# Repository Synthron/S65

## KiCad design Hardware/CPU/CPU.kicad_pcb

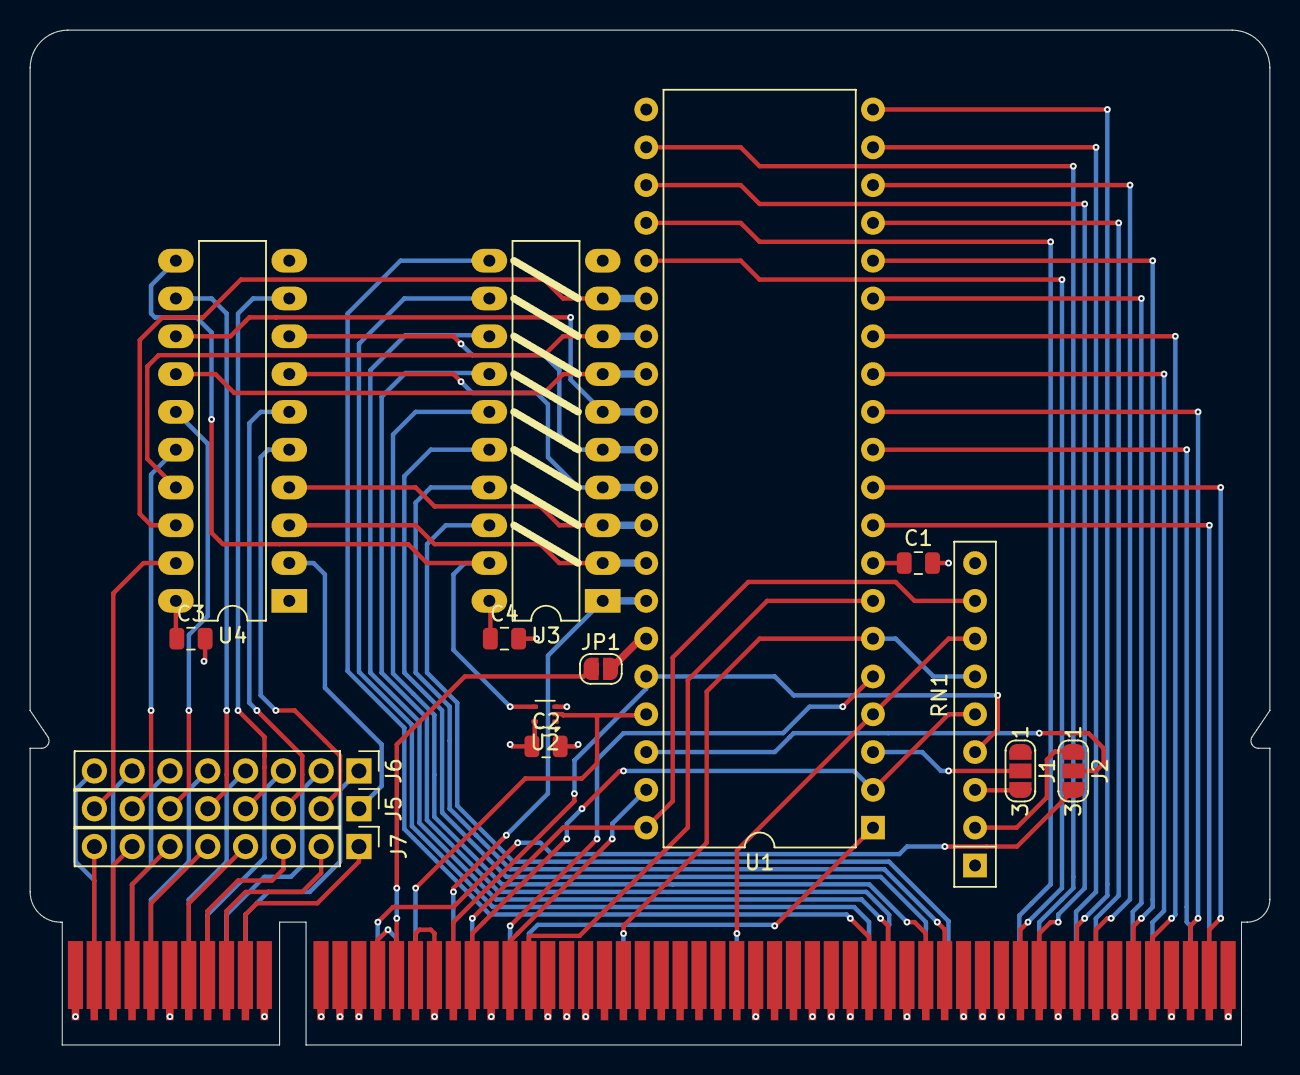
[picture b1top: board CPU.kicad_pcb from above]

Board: 4 copper layers, 83.3 x 68.2 mm, 16 parts (1 on the bottom side), 78 nets.

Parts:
C1, C2, C3, C4: 100n; C_0805_2012Metric
J1: ABORT; SolderJumper-3_P1.3mm_Open_RoundedPad1.0x1.5mm_NumberLabels
J2: SO/MX; SolderJumper-3_P1.3mm_Open_RoundedPad1.0x1.5mm_NumberLabels
J3: Bus_PCI_6502; BUS_PCI
J5: Bank Bridge A; PinHeader_1x08_P2.54mm_Vertical
J6: Bank Bridge B; PinHeader_1x08_P2.54mm_Vertical
J7: Bank Bridge C; PinHeader_1x08_P2.54mm_Vertical
JP1: E; SolderJumper-2_P1.3mm_Open_RoundedPad1.0x1.5mm
RN1: 3k3; R_Array_SIP9
U1: 65C02 / 65816; DIP-40_W15.24mm
U2: 74LVC1GU04DRL; SOT-553
U3: 74HC245; DIP-20_W7.62mm_LongPads
U4: 74HC373; DIP-20_W7.62mm_LongPads

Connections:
+5V: C1.1, C2.1, C3.1, C4.1, J3.A14 (5V), J3.A22 (5V), J3.A36 (5V), J3.A47 (5V), J3.B14 (5V), J3.B22 (5V), J3.B36 (5V), J3.B47 (5V), RN1.1 (common), U1.8 (VDD), U2.5 (VCC), U3.20 (VCC), U4.20 (VCC)
+9V: J3.A49 (9V), J3.B49 (9V)
/A0: J3.B2 (A0), U1.9 (A0)
/A1: J3.A2 (A1), U1.10 (A1)
/A2: J3.B3 (A2), U1.11 (A2)
/A3: J3.A3, U1.12 (A3)
/A4: J3.B5 (A4), U1.13 (A4)
/A5: J3.A5, U1.14 (A5)
/A6: J3.B6 (A6), U1.15 (A6)
/A7: J3.A6 (A7), U1.16 (A7)
/A8: J3.B8 (A8), U1.17 (A8)
/A9: J3.A8 (A9), U1.18 (A9)
/A10: J3.B9 (A10), U1.19 (A10)
/A11: J3.A9 (A11), U1.20 (A11)
/A12: J3.B11 (A12), U1.22 (A12)
/A13: J3.A11 (A13), U1.23 (A13)
/A14: J3.B12 (A14), U1.24 (A14)
/A15: J3.A12 (A15), U1.25 (A15)
/BA0: J5.1, U4.2 (O0)
/BA1: J5.2, U4.5 (O1)
/BA2: J5.3, U4.6 (O2)
/BA3: J5.4, U4.9 (O3)
/BA4: J5.5, U4.12 (O4)
/BA5: J5.6, U4.15 (O5)
/BA6: J5.7, U4.16 (O6)
/BA7: J5.8, U4.19 (O7)
/CLK: J3.B44 (CLK), U1.37 (ϕ0), U2.2
/D0: J3.B16 (D0), U3.18 (B0)
/D1: J3.A16 (D1), U3.17 (B1)
/D2: J3.B17 (D2), U3.16 (B2)
/D3: J3.A17 (D3), U3.15 (B3)
/D4: J3.B19 (D4), U3.14 (B4)
/D5: J3.A19 (D5), U3.13 (B5)
/D6: J3.B20 (D6), U3.12 (B6)
/D7: J3.A20 (D7), U3.11 (B7)
/E: J3.A45 (E), JP1.1 (A)
/M/X: J2.3, J3.B46 (M/~X)
/RAM_0: J3.A53 (RAM0), J7.1
/RAM_1: J3.A54 (RAM1), J7.2
/RAM_2: J3.A55 (RAM2), J7.3
/RAM_3: J3.A56 (RAM3), J7.4
/RAM_4: J3.A58 (RAM4), J7.5
/RAM_5: J3.A59 (RAM5), J7.6
/RAM_6: J3.A60 (RAM6), J7.7
/RAM_7: J3.A61 (RAM7), J7.8
/ROM_0: J3.B53 (ROM0), J6.1
/ROM_1: J3.B54 (ROM1), J6.2
/ROM_2: J3.B55 (ROM2), J6.3
/ROM_3: J3.B56 (ROM3), J6.4
/ROM_4: J3.B58 (ROM4), J6.5
/ROM_5: J3.B59 (ROM5), J6.6
/ROM_6: J3.B60 (ROM6), J6.7
/ROM_7: J3.B61 (ROM7), J6.8
/R/~W: J3.B42 (R/~W), U1.34 (R/~W), U3.1 (A->B)
/SYNC_VPA: J3.A38 (Sync/VPA), U1.7 (SYNC)
/~BE: J3.A42 (~BE), RN1.4 (R3), U1.36 (BE)
/~IRQ: J3.B27 (~IRQ), RN1.7 (R6), U1.4 (~IRQ)
/~ML: J3.B39 (~ML), U1.5 (~ML)
/~NMI: J3.B33 (~NMI), RN1.6 (R5), U1.6 (~NMI)
/~RDY: J3.A41 (~RDY), RN1.5 (R4), U1.2 (RDY)
/~RES: J3.B41 (~RES), RN1.8 (R7), U1.40 (~RES)
/~VP: J3.B38 (~VP), U1.1 (~VP)
/Ø2/VDA: J3.A39 (Ø2/VDA), U1.39 (ϕ2)
GND: C1.2, C2.2, C3.2, C4.2, J3.A1 (GND), J3.A4 (GND), J3.A7 (GND), J3.A10 (GND), J3.A13 (GND), J3.A15 (GND), J3.A18 (GND), J3.A21 (GND), J3.A23 (GND), J3.A26 (GND), J3.A35 (GND), J3.A37 (GND), J3.A40 (GND), J3.A43 (GND), J3.A44 (GND), J3.A46 (GND), J3.A48 (GND), J3.A52 (GND), J3.A57 (GND), J3.A62 (GND), J3.B1 (GND), J3.B4 (GND), J3.B7 (GND), J3.B10 (GND), J3.B13 (GND), J3.B15 (GND), J3.B18 (GND), J3.B21 (GND), J3.B23 (GND), J3.B26 (GND), J3.B35 (GND), J3.B37 (GND), J3.B40 (GND), J3.B43 (GND), J3.B45 (GND), J3.B48 (GND), J3.B52 (GND), J3.B57 (GND), J3.B62 (GND), U1.21 (VSS), U2.3 (GND), U3.10 (GND), U4.10 (GND)
unnamed: J1.2, U1.3 (ϕ1)
unnamed: J1.3, RN1.3 (R2)
unnamed: J2.1, RN1.2 (R1)
unnamed: J2.2, U1.38 (~SO)
unnamed: JP1.2 (B), U1.35 (nc)
unnamed: U1.33 (D0), U3.2 (A0), U4.3 (D0)
unnamed: U1.32 (D1), U3.3 (A1), U4.4 (D1)
unnamed: U1.31 (D2), U3.4 (A2), U4.7 (D2)
unnamed: U1.30 (D3), U3.5 (A3), U4.8 (D3)
unnamed: U1.29 (D4), U3.6 (A4), U4.13 (D4)
unnamed: U1.28 (D5), U3.7 (A5), U4.14 (D5)
unnamed: U1.27 (D6), U3.8 (A6), U4.17 (D6)
unnamed: U1.26 (D7), U3.9 (A7), U4.18 (D7)
unnamed: U2.4, U3.19 (CE), U4.11 (LE)

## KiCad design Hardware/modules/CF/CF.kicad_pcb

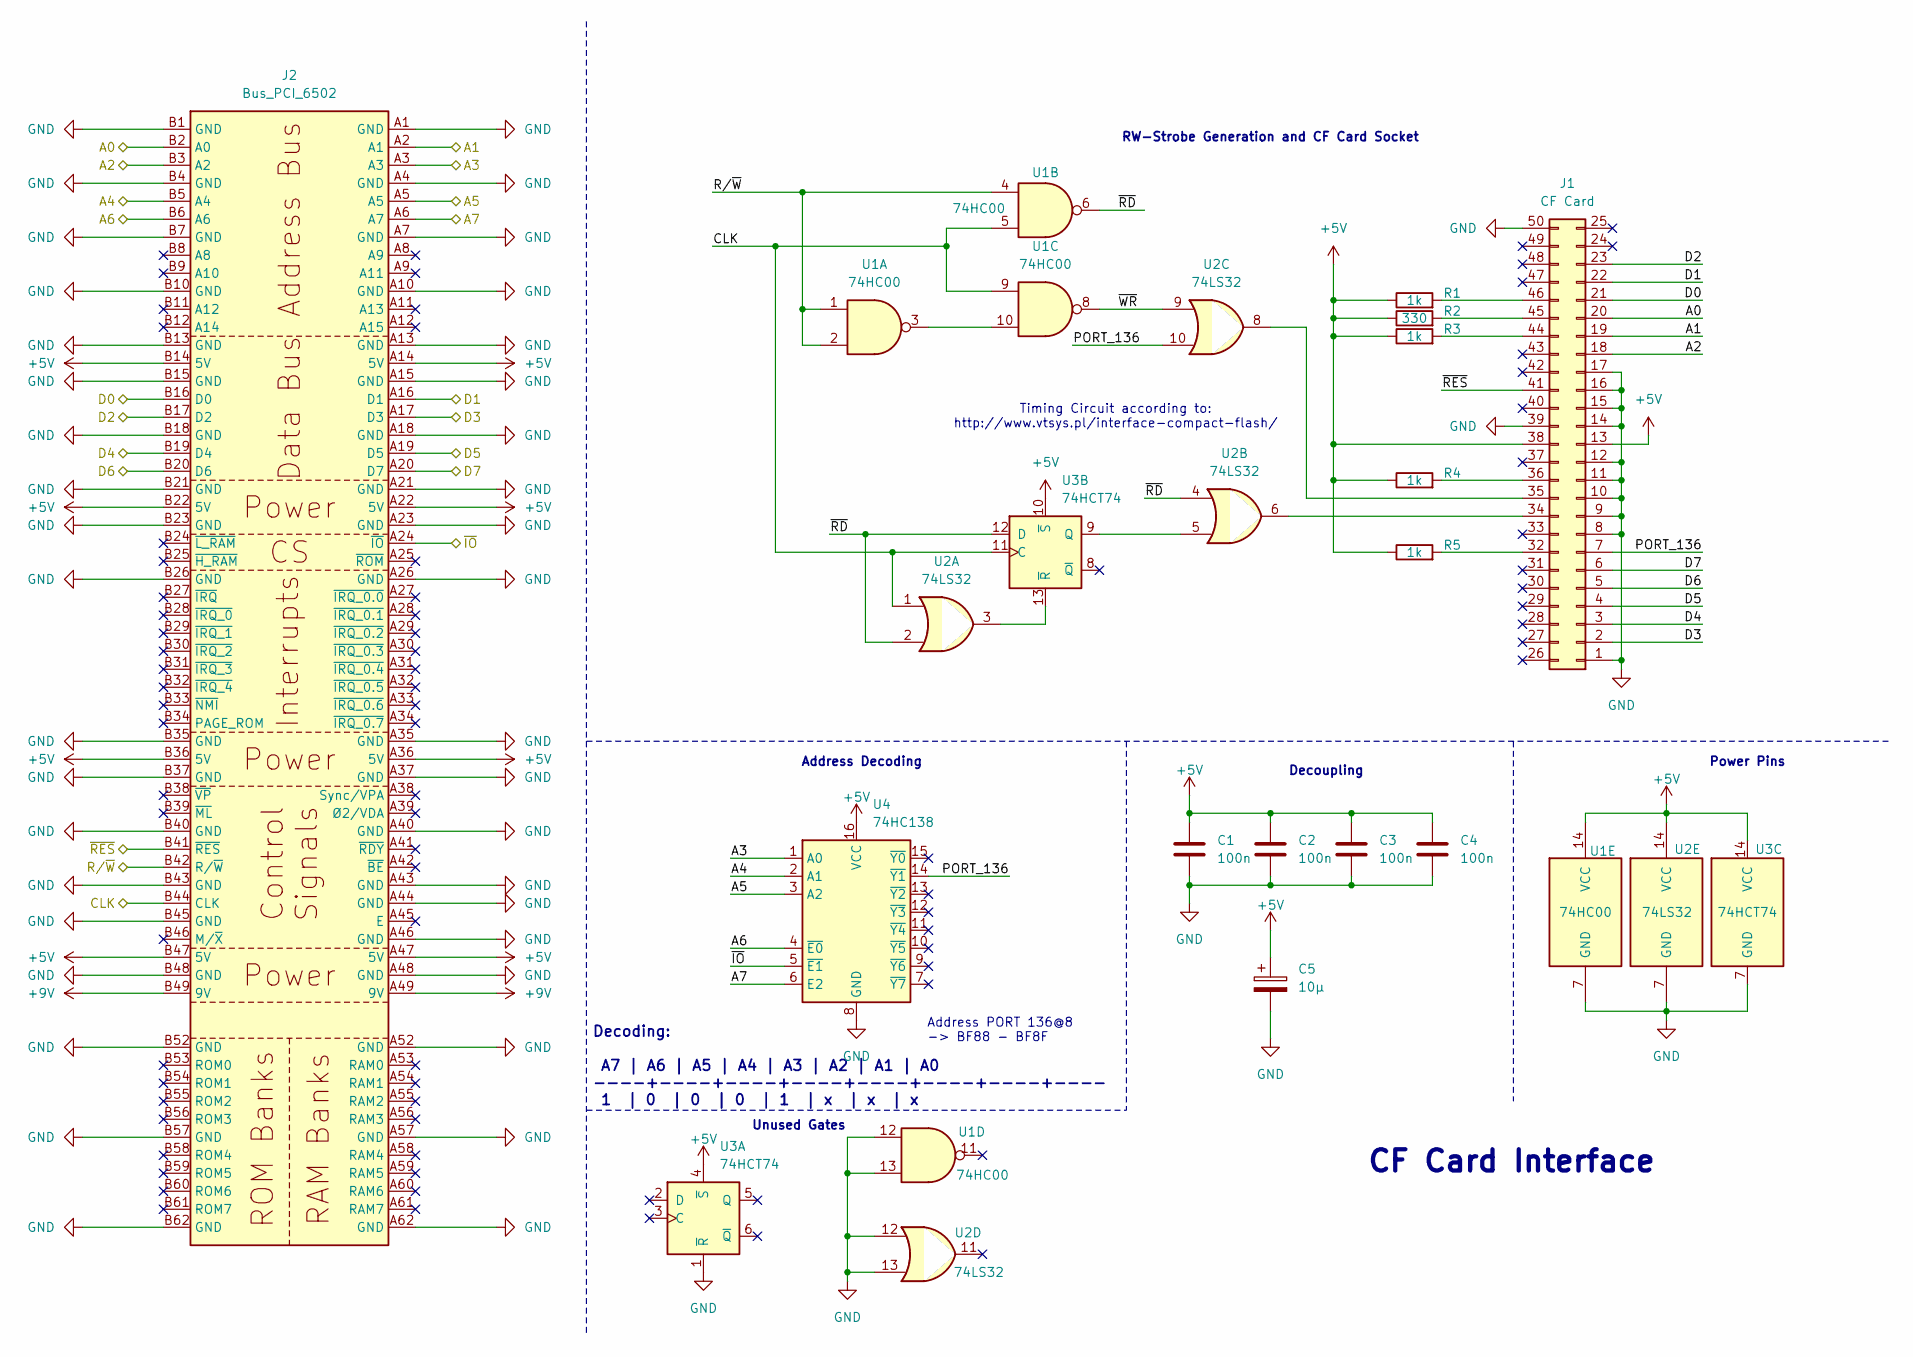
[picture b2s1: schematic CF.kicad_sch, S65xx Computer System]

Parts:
C1, C2, C3, C4: 100n; C_0805_2012Metric
C5: 10µ; CP_Radial_D5.0mm_P2.50mm
J1: CF Card; CF-Card_3M_N7E50-A516xx-30
J2: Bus_PCI_6502; BUS_PCI
R1, R3, R4, R5: 1k; R_0805_2012Metric
R2: 330; R_0805_2012Metric
U1: 74HC00; DIP-14_W7.62mm
U2: 74LS32; DIP-14_W7.62mm
U3: 74HCT74; DIP-14_W7.62mm
U4: 74HC138; DIP-16_W7.62mm

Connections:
+5V: C1.1, C2.1, C3.1, C4.1, C5.1, J1.13, J1.38, J2.A14 (5V), J2.A22 (5V), J2.A36 (5V), J2.A47 (5V), J2.B14 (5V), J2.B22 (5V), J2.B36 (5V), J2.B47 (5V), R1.1, R2.1, R3.1, R4.1, R5.1, U1.14 (VCC), U2.14 (VCC), U3.4 (~S), U3.10 (~S), U3.14 (VCC), U4.16 (VCC)
+9V: J2.A49 (9V), J2.B49 (9V)
/A0: J1.20, J2.B2 (A0)
/A1: J1.19, J2.A2 (A1)
/A2: J1.18, J2.B3 (A2)
/A3: J2.A3, U4.1 (A0)
/A4: J2.B5 (A4), U4.2 (A1)
/A5: J2.A5, U4.3 (A2)
/A6: J2.B6 (A6), U4.4 (~E0)
/A7: J2.A6 (A7), U4.6 (E2)
/CLK: J2.B44 (CLK), U1.5, U1.9, U2.1, U3.11 (C)
/D0: J1.21, J2.B16 (D0)
/D1: J1.22, J2.A16 (D1)
/D2: J1.23, J2.B17 (D2)
/D3: J1.2, J2.A17 (D3)
/D4: J1.3, J2.B19 (D4)
/D5: J1.4, J2.A19 (D5)
/D6: J1.5, J2.B20 (D6)
/D7: J1.6, J2.A20 (D7)
/PORT_136: J1.7, U2.10, U4.14 (~Y1)
/R/~W: J2.B42 (R/~W), U1.1, U1.2, U1.4
/~IO: J2.A24 (~IO), U4.5 (~E1)
/~RD: U1.6, U2.2, U2.4, U3.12 (D)
/~RES: J1.41, J2.B41 (~RES)
/~WR: U1.8, U2.9
GND: C1.2, C2.2, C3.2, C4.2, C5.2, J1.1, J1.8, J1.9, J1.10, J1.11, J1.12, J1.14, J1.15, J1.16, J1.17, J1.39, J1.50, J2.A1 (GND), J2.A4 (GND), J2.A7 (GND), J2.A10 (GND), J2.A13 (GND), J2.A15 (GND), J2.A18 (GND), J2.A21 (GND), J2.A23 (GND), J2.A26 (GND), J2.A35 (GND), J2.A37 (GND), J2.A40 (GND), J2.A43 (GND), J2.A44 (GND), J2.A46 (GND), J2.A48 (GND), J2.A52 (GND), J2.A57 (GND), J2.A62 (GND), J2.B1 (GND), J2.B4 (GND), J2.B7 (GND), J2.B10 (GND), J2.B13 (GND), J2.B15 (GND), J2.B18 (GND), J2.B21 (GND), J2.B23 (GND), J2.B26 (GND), J2.B35 (GND), J2.B37 (GND), J2.B40 (GND), J2.B43 (GND), J2.B45 (GND), J2.B48 (GND), J2.B52 (GND), J2.B57 (GND), J2.B62 (GND), U1.7 (GND), U1.12, U1.13, U2.7 (GND), U2.12, U2.13, U3.1 (~R), U3.7 (GND), U4.8 (GND)
unnamed: J1.32, R5.2
unnamed: J1.34, U2.6
unnamed: J1.35, U2.8
unnamed: J1.36, R4.2
unnamed: J1.44, R3.2
unnamed: J1.45, R2.2
unnamed: J1.46, R1.2
unnamed: U1.3, U1.10
unnamed: U2.5, U3.9 (Q)
unnamed: U2.3, U3.13 (~R)

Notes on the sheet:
Decoding: A7 | A6 | A5 | A4 | A3 | A2 | A1 | A0 ----+----+----+----+----+----+----+---- 1 | 0 | 0 | 0 | 1 | x | x | x
Power Pins
Address Decoding
Decoupling
CF Card Interface
Address PORT 136@8 -> BF88 - BF8F
Timing Circuit according to: http://www.vtsys.pl/interface-compact-flash/
RW-Strobe Generation and CF Card Socket
Unused Gates

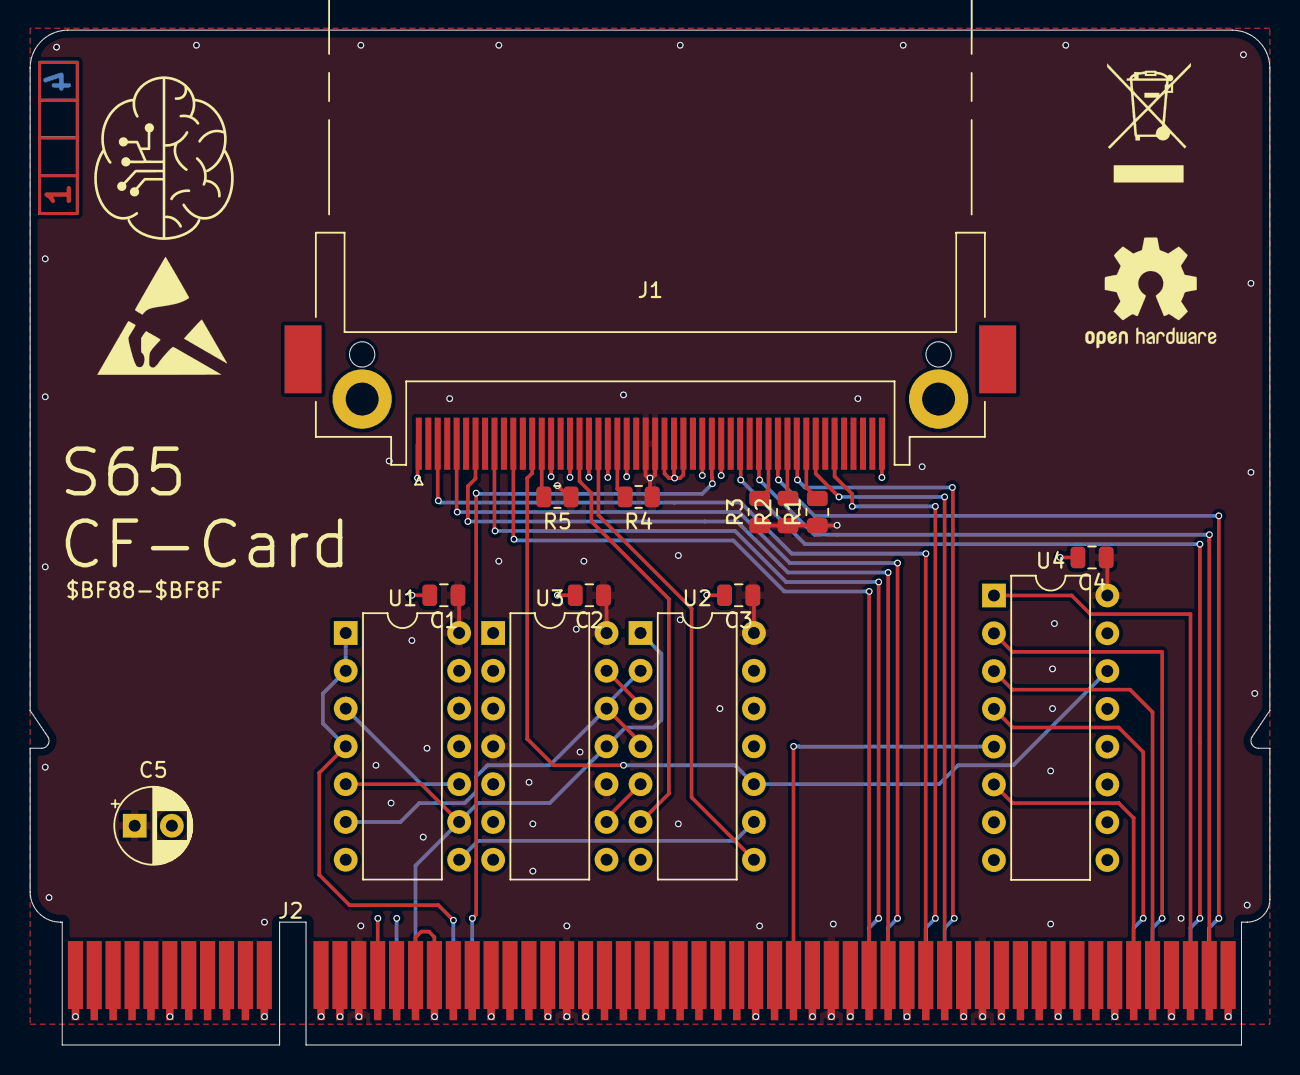
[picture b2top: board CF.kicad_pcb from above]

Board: 4 copper layers, 83.3 x 68.2 mm, 17 parts (1 on the bottom side), 36 nets.

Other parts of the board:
Ref**: Val**; ladder_4

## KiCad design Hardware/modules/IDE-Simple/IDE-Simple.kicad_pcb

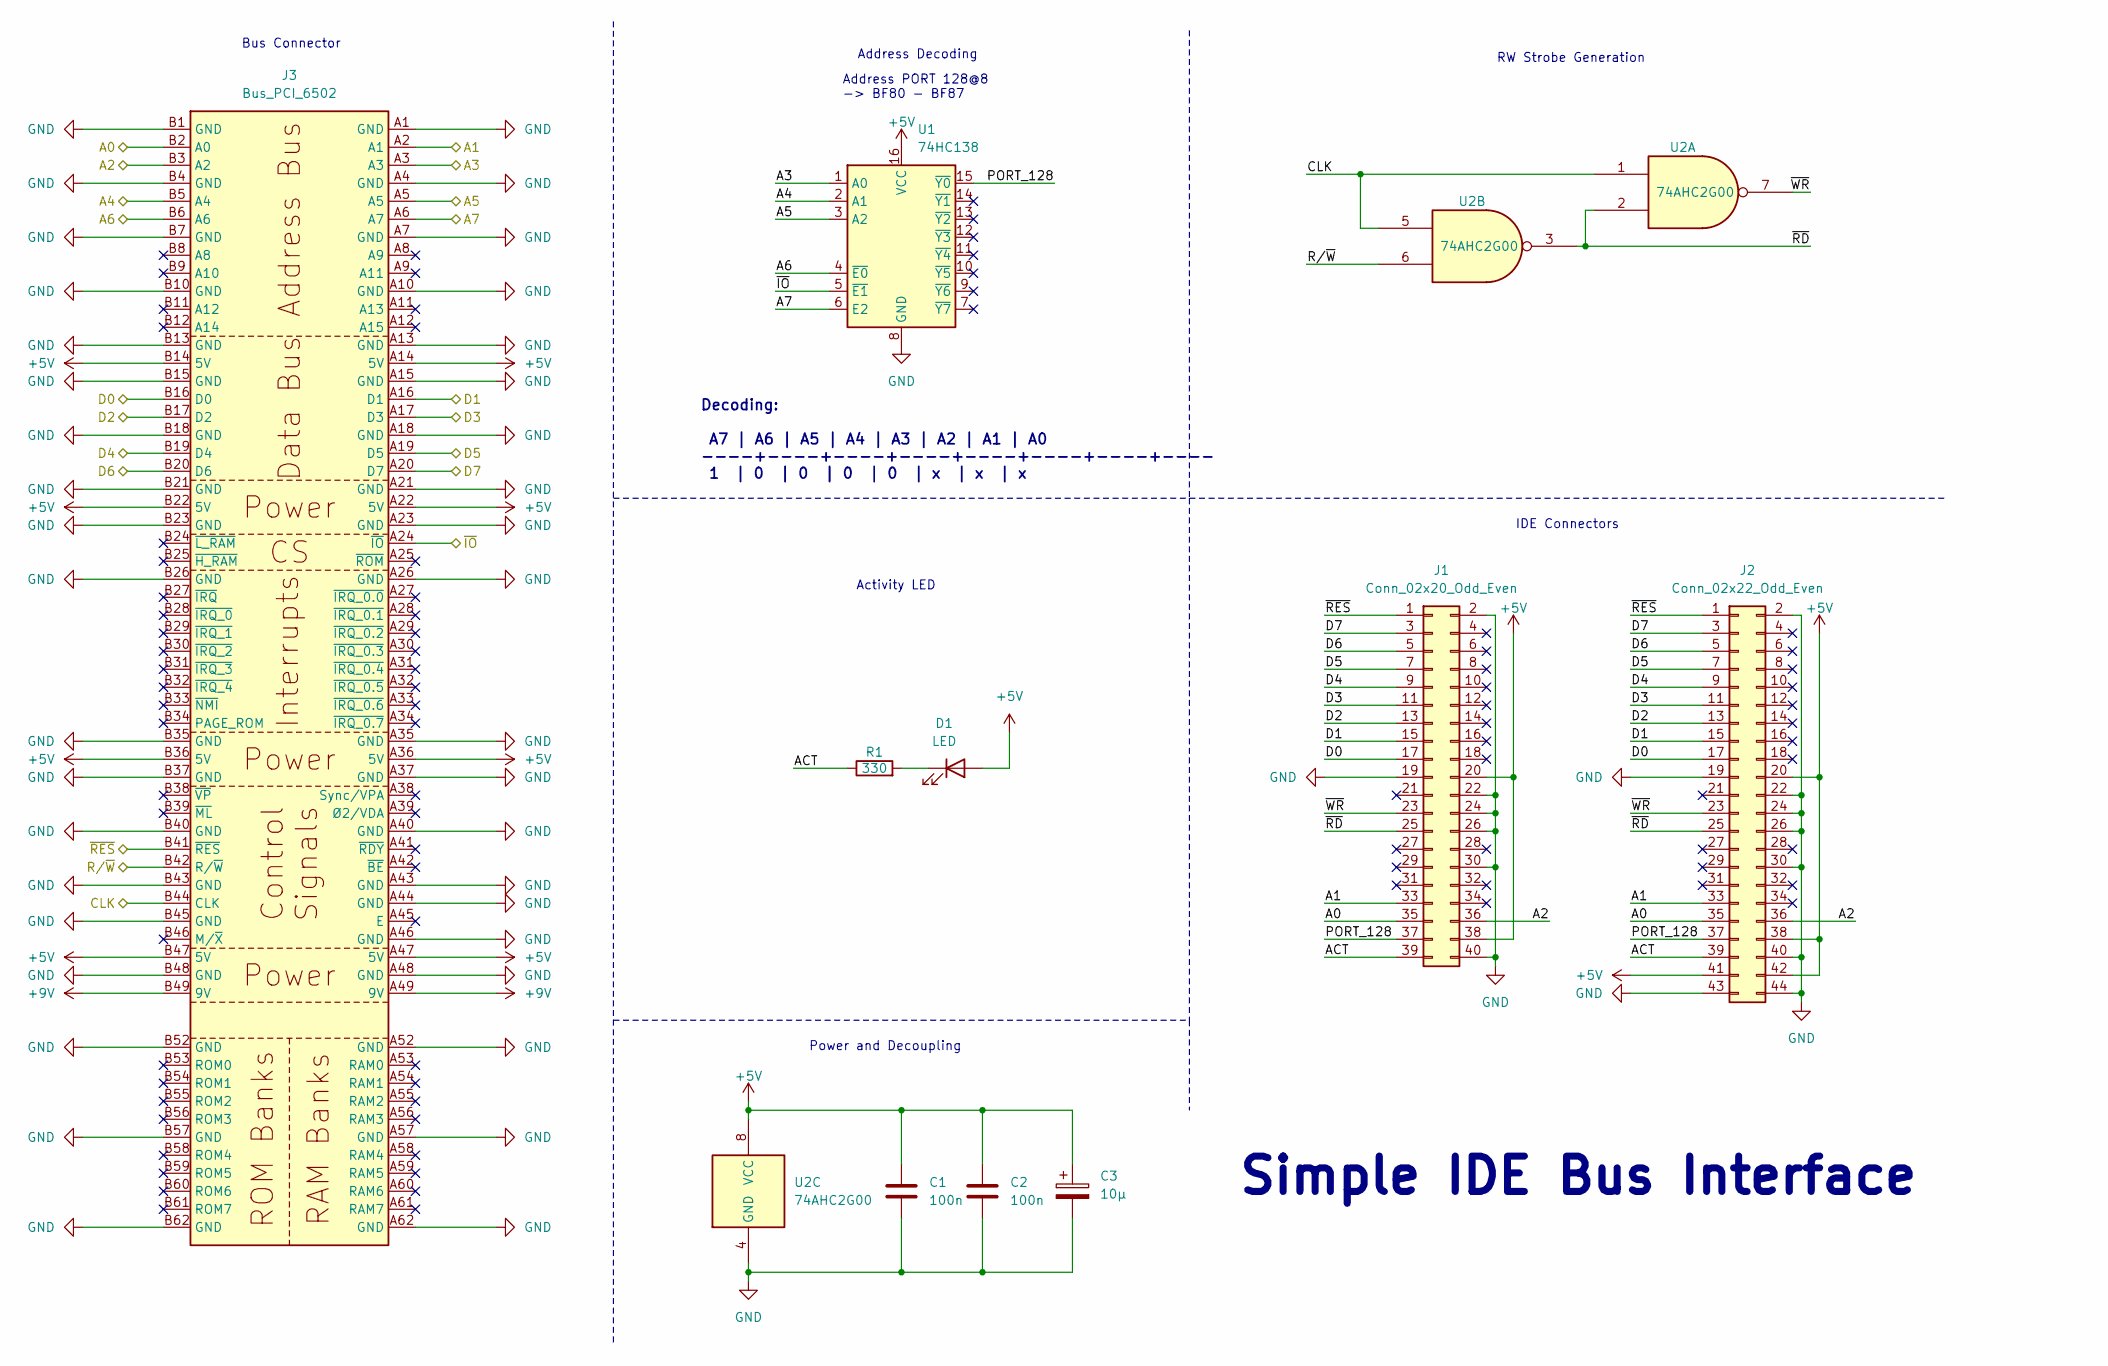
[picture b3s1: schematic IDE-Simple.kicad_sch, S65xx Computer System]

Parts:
C1, C2: 100n; C_0805_2012Metric
C3: 10µ; CP_Radial_D5.0mm_P2.50mm
D1: LED; LED_0805_2012Metric
J1: Conn_02x20_Odd_Even; IDC-Header_2x20_P2.54mm_Vertical
J2: Conn_02x22_Odd_Even; PinHeader_2x22_P2.00mm_Vertical
J3: Bus_PCI_6502; BUS_PCI
R1: 330; R_0805_2012Metric
U1: 74HC138; DIP-16_W7.62mm
U2: 74AHC2G00; TSSOP-8_3x3mm_P0.65mm

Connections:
+5V: C1.1, C2.1, C3.1, D1.2 (A), J1.20, J1.38, J2.20, J2.38, J2.41, J2.42, J3.A14 (5V), J3.A22 (5V), J3.A36 (5V), J3.A47 (5V), J3.B14 (5V), J3.B22 (5V), J3.B36 (5V), J3.B47 (5V), U1.16 (VCC), U2.8 (VCC)
+9V: J3.A49 (9V), J3.B49 (9V)
/A0: J1.35, J2.35, J3.B2 (A0)
/A1: J1.33, J2.33, J3.A2 (A1)
/A2: J1.36, J2.36, J3.B3 (A2)
/A3: J3.A3, U1.1 (A0)
/A4: J3.B5 (A4), U1.2 (A1)
/A5: J3.A5, U1.3 (A2)
/A6: J3.B6 (A6), U1.4 (~E0)
/A7: J3.A6 (A7), U1.6 (E2)
/ACT: J1.39, J2.39, R1.1
/CLK: J3.B44 (CLK), U2.1, U2.5
/D0: J1.17, J2.17, J3.B16 (D0)
/D1: J1.15, J2.15, J3.A16 (D1)
/D2: J1.13, J2.13, J3.B17 (D2)
/D3: J1.11, J2.11, J3.A17 (D3)
/D4: J1.9, J2.9, J3.B19 (D4)
/D5: J1.7, J2.7, J3.A19 (D5)
/D6: J1.5, J2.5, J3.B20 (D6)
/D7: J1.3, J2.3, J3.A20 (D7)
/PORT_128: J1.37, J2.37, U1.15 (~Y0)
/R/~W: J3.B42 (R/~W), U2.6
/~IO: J3.A24 (~IO), U1.5 (~E1)
/~RD: J1.25, J2.25, U2.2, U2.3
/~RES: J1.1, J2.1, J3.B41 (~RES)
/~WR: J1.23, J2.23, U2.7
GND: C1.2, C2.2, C3.2, J1.2, J1.19, J1.22, J1.24, J1.26, J1.30, J1.40, J2.2, J2.19, J2.22, J2.24, J2.26, J2.30, J2.40, J2.43, J2.44, J3.A1 (GND), J3.A4 (GND), J3.A7 (GND), J3.A10 (GND), J3.A13 (GND), J3.A15 (GND), J3.A18 (GND), J3.A21 (GND), J3.A23 (GND), J3.A26 (GND), J3.A35 (GND), J3.A37 (GND), J3.A40 (GND), J3.A43 (GND), J3.A44 (GND), J3.A46 (GND), J3.A48 (GND), J3.A52 (GND), J3.A57 (GND), J3.A62 (GND), J3.B1 (GND), J3.B4 (GND), J3.B7 (GND), J3.B10 (GND), J3.B13 (GND), J3.B15 (GND), J3.B18 (GND), J3.B21 (GND), J3.B23 (GND), J3.B26 (GND), J3.B35 (GND), J3.B37 (GND), J3.B40 (GND), J3.B43 (GND), J3.B45 (GND), J3.B48 (GND), J3.B52 (GND), J3.B57 (GND), J3.B62 (GND), U1.8 (GND), U2.4 (GND)

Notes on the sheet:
Address Decoding
Activity LED
Bus Connector
Address PORT 128@8 -> BF80 - BF87
Power and Decoupling
Decoding: A7 | A6 | A5 | A4 | A3 | A2 | A1 | A0 ----+----+----+----+----+----+----+---- 1 | 0 | 0 | 0 | 0 | x | x | x
IDE Connectors
RW Strobe Generation
Simple IDE Bus Interface

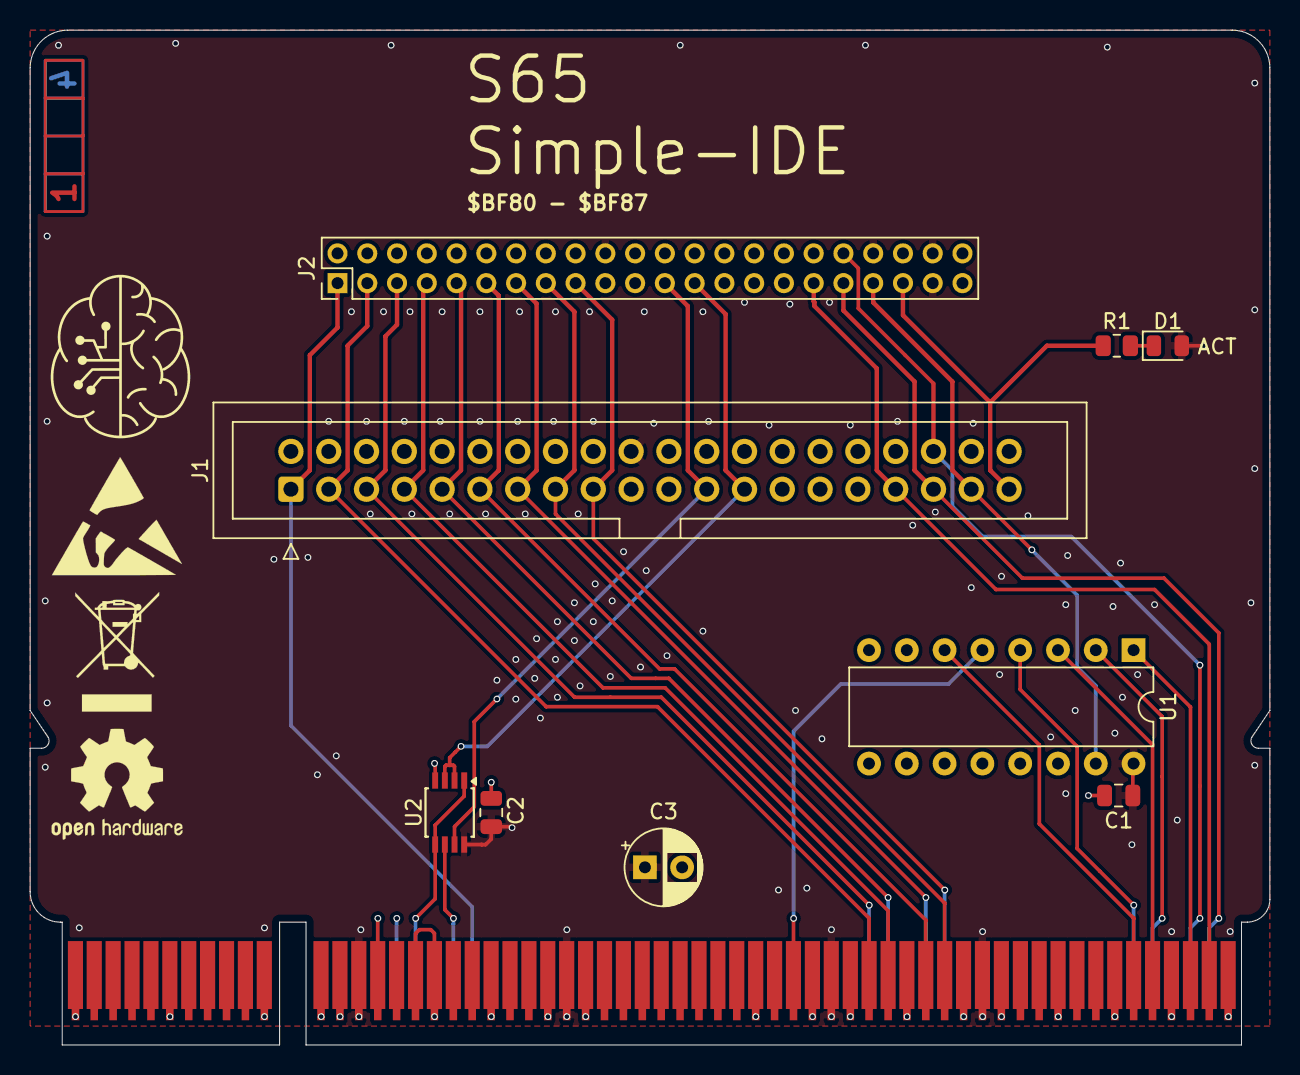
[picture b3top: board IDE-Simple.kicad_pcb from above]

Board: 4 copper layers, 83.3 x 68.2 mm, 11 parts (1 on the bottom side), 27 nets.

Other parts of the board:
Ref**: Val**; ladder_4

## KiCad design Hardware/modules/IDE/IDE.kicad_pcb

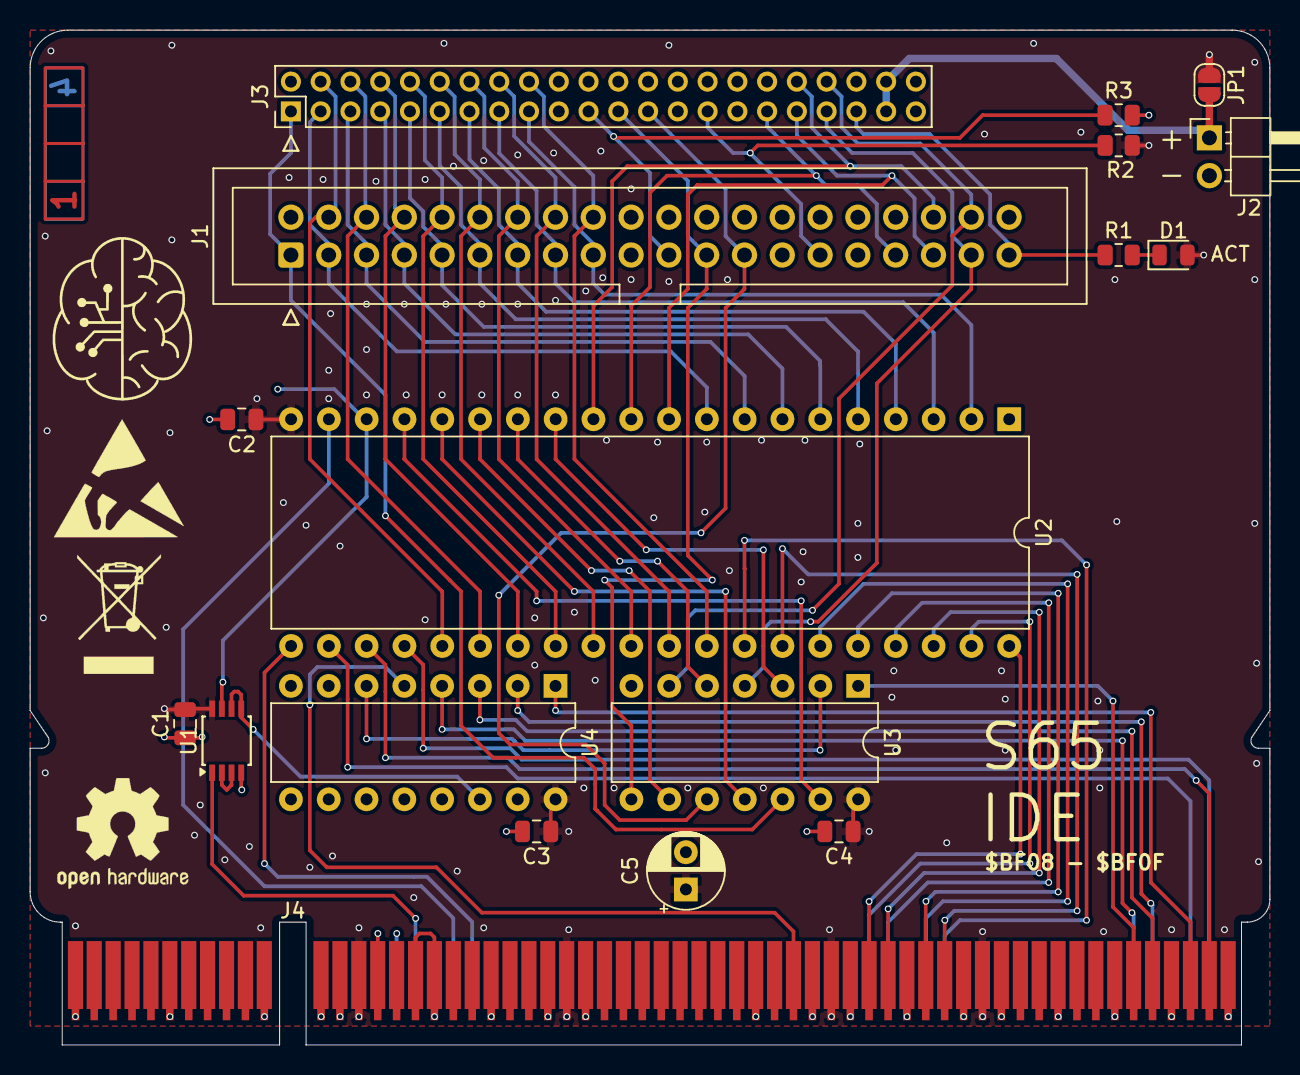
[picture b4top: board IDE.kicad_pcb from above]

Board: 4 copper layers, 83.3 x 68.2 mm, 19 parts (1 on the bottom side), 53 nets.

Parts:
C1, C2, C3, C4: 100n; C_0805_2012Metric
C5: 10µ; CP_Radial_D5.0mm_P2.50mm
D1: LED; LED_0805_2012Metric
J1: Conn_02x20_Odd_Even; IDC-Header_2x20_P2.54mm_Vertical
J2: IDE_VCC; PinHeader_1x02_P2.54mm_Horizontal
J3: Conn_02x22_Odd_Even; PinHeader_2x22_P2.00mm_Vertical
J4: Bus_PCI_6502; BUS_PCI
JP1: Jumper_2_Open; SolderJumper-2_P1.3mm_Open_RoundedPad1.0x1.5mm
R1: 330; R_0805_2012Metric
R2, R3: 10k; R_0805_2012Metric
Ref**: Val**; ladder_4
U1: 74AHC2G00; TSSOP-8_3x3mm_P0.65mm
U2: 6525; DIP-40_W15.24mm
U3: 74HCT04; DIP-14_W7.62mm
U4: 74HC138; DIP-16_W7.62mm

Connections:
+5V: C1.1, C2.1, C3.1, C4.1, C5.1, D1.2 (A), J4.A14 (5V), J4.A22 (5V), J4.A36 (5V), J4.A47 (5V), J4.B14 (5V), J4.B22 (5V), J4.B36 (5V), J4.B47 (5V), JP1.1 (A), R2.2, U1.8 (VCC), U2.20 (VDD), U3.14 (VCC), U4.16 (VCC)
+9V: J4.A49 (9V), J4.B49 (9V)
/A0: J4.B2 (A0), U2.24 (RS0)
/A1: J4.A2 (A1), U2.23 (RS1)
/A2: J4.B3 (A2), U2.22 (RS2)
/A3: J4.A3, U4.1 (A0)
/A4: J4.B5 (A4), U4.2 (A1)
/A5: J4.A5, U4.3 (A2)
/A6: J4.B6 (A6), U4.4 (~E0)
/A7: J4.A6 (A7), U3.1
/ACT: J1.39, J3.39, R1.1
/CLK: J4.B44 (CLK), U1.1
/D0: J4.B16 (D0), U2.33 (D0)
/D1: J4.A16 (D1), U2.34 (D1)
/D2: J4.B17 (D2), U2.35 (D2)
/D3: J4.A17 (D3), U2.36 (D3)
/D4: J4.B19 (D4), U2.37 (D4)
/D5: J4.A19 (D5), U2.38 (D5)
/D6: J4.B20 (D6), U2.39 (D6)
/D7: J4.A20 (D7), U2.40 (D7)
/DA0: J1.35, J3.35, U2.10 (PB0)
/DA1: J1.33, J3.33, U2.11 (PB1)
/DA2: J1.36, J3.36, U2.12 (PB2)
/DCS0: J1.37, J3.37, U3.4
/DCS1: J1.38, J3.38, U3.6
/DIOR: J1.25, J3.25, U3.10
/DIOW: J1.23, J3.23, U3.8
/DMACK: J1.29, J3.29, R2.1
/DMARQ: J1.21, J3.21, R3.1
/DRESET: J1.1, J3.1, U3.12
/IDEVCC: J2.1, J3.41, J3.42, JP1.2 (B)
/PA0: J1.17, J3.17, U2.2 (PA0)
/PA1: J1.15, J3.15, U2.3 (PA1)
/PA2: J1.13, J3.13, U2.4 (PA2)
/PA3: J1.11, J3.11, U2.5 (PA3)
/PA4: J1.9, J3.9, U2.6 (PA4)
/PA5: J1.7, J3.7, U2.7 (PA5)
/PA6: J1.5, J3.5, U2.8 (PA6)
/PA7: J1.3, J3.3, U2.9 (PA7)
/PB0: J1.4, J3.4, U2.25 (PC0)
/PB1: J1.6, J3.6, U2.26 (PC1)
/PB2: J1.8, J3.8, U2.27 (PC2)
/PB3: J1.10, J3.10, U2.28 (PC3)
/PB4: J1.12, J3.12, U2.29 (PC4)
/PB5: J1.14, J3.14, U2.30 (PC5)
/PB6: J1.16, J3.16, U2.31 (PC6)
/PB7: J1.18, J3.18, U2.32 (PC7)
/PORT_8: U1.2, U1.3
/R/~W: J4.B42 (R/~W), U2.19 (R/~W)
/~IO: J4.A24 (~IO), U4.5 (~E1)
/~RES: J4.B41 (~RES), U2.21 (~RST)
GND: C1.2, C2.2, C3.2, C4.2, C5.2, J1.2, J1.19, J1.22, J1.24, J1.26, J1.28, J1.30, J1.40, J2.2, J3.2, J3.19, J3.22, J3.24, J3.26, J3.28, J3.30, J3.40, J3.43, J3.44, J4.A1 (GND), J4.A4 (GND), J4.A7 (GND), J4.A10 (GND), J4.A13 (GND), J4.A15 (GND), J4.A18 (GND), J4.A21 (GND), J4.A23 (GND), J4.A26 (GND), J4.A35 (GND), J4.A37 (GND), J4.A40 (GND), J4.A43 (GND), J4.A44 (GND), J4.A46 (GND), J4.A48 (GND), J4.A52 (GND), J4.A57 (GND), J4.A62 (GND), J4.B1 (GND), J4.B4 (GND), J4.B7 (GND), J4.B10 (GND), J4.B13 (GND), J4.B15 (GND), J4.B18 (GND), J4.B21 (GND), J4.B23 (GND), J4.B26 (GND), J4.B35 (GND), J4.B37 (GND), J4.B40 (GND), J4.B43 (GND), J4.B45 (GND), J4.B48 (GND), J4.B52 (GND), J4.B57 (GND), J4.B62 (GND), R3.2, U1.4 (GND), U2.1 (VSS), U3.7 (GND), U4.8 (GND)
unnamed: U1.5, U1.6, U4.14 (~Y1)
